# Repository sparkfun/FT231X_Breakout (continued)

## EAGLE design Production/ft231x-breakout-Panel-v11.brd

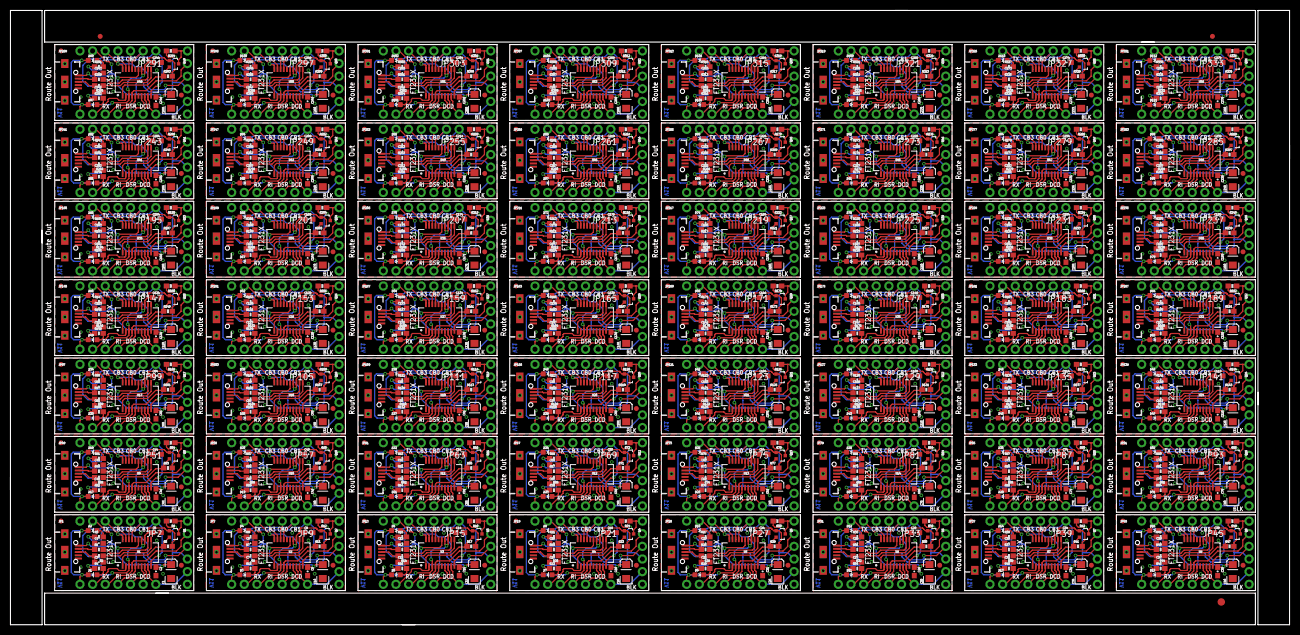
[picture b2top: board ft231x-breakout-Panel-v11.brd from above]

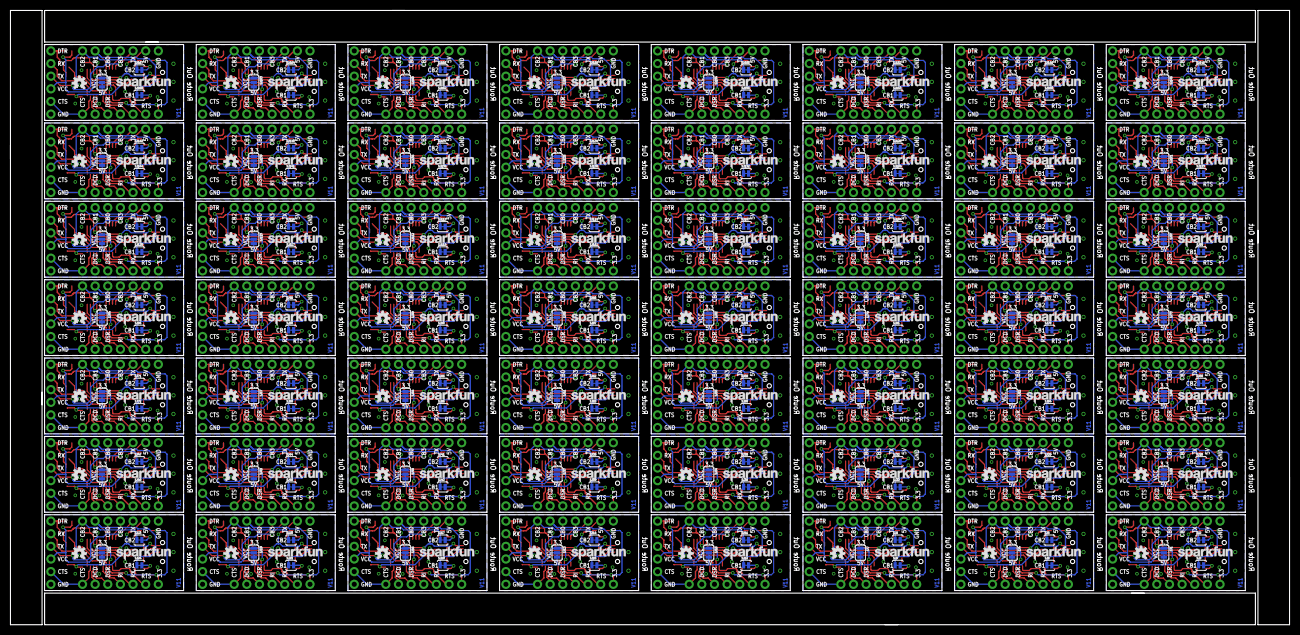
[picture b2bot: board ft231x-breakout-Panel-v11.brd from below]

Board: 2 copper layers, 257.0 x 123.4 mm, 1459 parts (280 on the bottom side), 1400 nets.

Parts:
C1, C10, C15, C20, C25, C30, C35, C40, C45, C50, C55, C60, C65, C70, C75, C80, C85, C90, C95, C100, C105, C110, C115, C120, C125, C130, C135, C140, C145, C150, C155, C160, C165, C170, C175, C180, C185, C190, C195, C200, C205, C210, C215, C220, C225, C230, C235, C240, C245, C250, C255, C260, C265, C270, C275, C280: 10uF; EIA3216
C2, C5, C6, C9, C11, C14, C16, C19, C21, C24, C26, C29, C31, C34, C36, C39, C41, C44, C46, C49, C51, C54, C56, C59, C61, C64, C66, C69, C71, C74, C76, C79, C81, C84, C86, C89, C91, C94, C96, C99, C101, C104, C106, C109, C111, C114, C116, C119, C121, C124, C126, C129, C131, C134, C136, C139, C141, C144, C146, C149, C151, C154, C156, C159, C161, C164, C166, C169, C171, C174, C176, C179, C181, C184, C186, C189, C191, C194, C196, C199, C201, C204, C206, C209, C211, C214, C216, C219, C221, C224, C226, C229, C231, C234, C236, C239, C241, C244, C246, C249, C251, C254, C256, C259, C261, C264, C266, C269, C271, C274, C276, C279: 0.1uF; 0603-CAP
C3, C4, C7, C8, C12, C13, C17, C18, C22, C23, C27, C28, C32, C33, C37, C38, C42, C43, C47, C48, C52, C53, C57, C58, C62, C63, C67, C68, C72, C73, C77, C78, C82, C83, C87, C88, C92, C93, C97, C98, C102, C103, C107, C108, C112, C113, C117, C118, C122, C123, C127, C128, C132, C133, C137, C138, C142, C143, C147, C148, C152, C153, C157, C158, C162, C163, C167, C168, C172, C173, C177, C178, C182, C183, C187, C188, C192, C193, C197, C198, C202, C203, C207, C208, C212, C213, C217, C218, C222, C223, C227, C228, C232, C233, C237, C238, C242, C243, C247, C248, C252, C253, C257, C258, C262, C263, C267, C268, C272, C273, C277, C278: 47pF; 0603-CAP
D1, D3, D5, D7, D9, D11, D13, D15, D17, D19, D21, D23, D25, D27, D29, D31, D33, D35, D37, D39, D41, D43, D45, D47, D49, D51, D53, D55, D57, D59, D61, D63, D65, D67, D69, D71, D73, D75, D77, D79, D81, D83, D85, D87, D89, D91, D93, D95, D97, D99, D101, D103, D105, D107, D109, D111: RED; LED-0603
D2, D4, D6, D8, D10, D12, D14, D16, D18, D20, D22, D24, D26, D28, D30, D32, D34, D36, D38, D40, D42, D44, D46, D48, D50, D52, D54, D56, D58, D60, D62, D64, D66, D68, D70, D72, D74, D76, D78, D80, D82, D84, D86, D88, D90, D92, D94, D96, D98, D100, D102, D104, D106, D108, D110, D112: Yellow; LED-0603
E$1: FIDUCIAL-1.5X3
E$5, E$6: FIDUCIAL-1X2
JP1, JP7, JP13, JP19, JP25, JP31, JP37, JP43, JP49, JP55, JP61, JP67, JP73, JP79, JP85, JP91, JP97, JP103, JP109, JP115, JP121, JP127, JP133, JP139, JP145, JP151, JP157, JP163, JP169, JP175, JP181, JP187, JP193, JP199, JP205, JP211, JP217, JP223, JP229, JP235, JP241, JP247, JP253, JP259, JP265, JP271, JP277, JP283, JP289, JP295, JP301, JP307, JP313, JP319, JP325, JP331: USB-MICROB"; USB-B-MICRO-SMD_V03
JP2, JP4, JP9, JP10, JP15, JP16, JP21, JP22, JP27, JP28, JP33, JP34, JP39, JP40, JP45, JP46, JP51, JP52, JP57, JP58, JP63, JP64, JP69, JP70, JP75, JP76, JP81, JP82, JP87, JP88, JP93, JP94, JP99, JP100, JP105, JP106, JP111, JP112, JP117, JP118, JP123, JP124, JP129, JP130, JP135, JP136, JP141, JP142, JP147, JP148, JP153, JP154, JP159, JP160, JP165, JP166, JP171, JP172, JP177, JP178, JP183, JP184, JP189, JP190, JP195, JP196, JP201, JP202, JP207, JP208, JP213, JP214, JP219, JP220, JP225, JP226, JP231, JP232, JP237, JP238, JP243, JP244, JP249, JP250, JP255, JP256, JP261, JP262, JP267, JP268, JP273, JP274, JP279, JP280, JP285, JP286, JP291, JP292, JP297, JP298, JP303, JP304, JP309, JP310, JP315, JP316, JP321, JP322, JP327, JP328, JP333, JP334: 1X07_NO_SILK
JP3, JP8, JP14, JP20, JP26, JP32, JP38, JP44, JP50, JP56, JP62, JP68, JP74, JP80, JP86, JP92, JP98, JP104, JP110, JP116, JP122, JP128, JP134, JP140, JP146, JP152, JP158, JP164, JP170, JP176, JP182, JP188, JP194, JP200, JP206, JP212, JP218, JP224, JP230, JP236, JP242, JP248, JP254, JP260, JP266, JP272, JP278, JP284, JP290, JP296, JP302, JP308, JP314, JP320, JP326, JP332: 1X06_NO_SILK
JP5, JP6, JP11, JP12, JP17, JP18, JP23, JP24, JP29, JP30, JP35, JP36, JP41, JP42, JP47, JP48, JP53, JP54, JP59, JP60, JP65, JP66, JP71, JP72, JP77, JP78, JP83, JP84, JP89, JP90, JP95, JP96, JP101, JP102, JP107, JP108, JP113, JP114, JP119, JP120, JP125, JP126, JP131, JP132, JP137, JP138, JP143, JP144, JP149, JP150, JP155, JP156, JP161, JP162, JP167, JP168, JP173, JP174, JP179, JP180, JP185, JP186, JP191, JP192, JP197, JP198, JP203, JP204, JP209, JP210, JP215, JP216, JP221, JP222, JP227, JP228, JP233, JP234, JP239, JP240, JP245, JP246, JP251, JP252, JP257, JP258, JP263, JP264, JP269, JP270, JP275, JP276, JP281, JP282, JP287, JP288, JP293, JP294, JP299, JP300, JP305, JP306, JP311, JP312, JP317, JP318, JP323, JP324, JP329, JP330, JP335, JP336: FIDUCIAL1X2; FIDUCIAL-1X2
LOGO1, LOGO2, LOGO3, LOGO4, LOGO5, LOGO6, LOGO7, LOGO8, LOGO9, LOGO10, LOGO11, LOGO12, LOGO13, LOGO14, LOGO15, LOGO16, LOGO17, LOGO18, LOGO19, LOGO20, LOGO21, LOGO22, LOGO23, LOGO24, LOGO25, LOGO26, LOGO27, LOGO28, LOGO29, LOGO30, LOGO31, LOGO32, LOGO33, LOGO34, LOGO35, LOGO36, LOGO37, LOGO38, LOGO39, LOGO40, LOGO41, LOGO42, LOGO43, LOGO44, LOGO45, LOGO46, LOGO47, LOGO48, LOGO49, LOGO50, LOGO51, LOGO52, LOGO53, LOGO54, LOGO55, LOGO56: SFE_LOGO_NAME.1_INCH; SFE_LOGO_NAME_.1
Q1, Q2, Q3, Q4, Q5, Q6, Q7, Q8, Q9, Q10, Q11, Q12, Q13, Q14, Q15, Q16, Q17, Q18, Q19, Q20, Q21, Q22, Q23, Q24, Q25, Q26, Q27, Q28, Q29, Q30, Q31, Q32, Q33, Q34, Q35, Q36, Q37, Q38, Q39, Q40, Q41, Q42, Q43, Q44, Q45, Q46, Q47, Q48, Q49, Q50, Q51, Q52, Q53, Q54, Q55, Q56: 2N7002PW; SOT323
R1, R2, R7, R8, R13, R14, R19, R20, R25, R26, R31, R32, R37, R38, R43, R44, R49, R50, R55, R56, R61, R62, R67, R68, R73, R74, R79, R80, R85, R86, R91, R92, R97, R98, R103, R104, R109, R110, R115, R116, R121, R122, R127, R128, R133, R134, R139, R140, R145, R146, R151, R152, R157, R158, R163, R164, R169, R170, R175, R176, R181, R182, R187, R188, R193, R194, R199, R200, R205, R206, R211, R212, R217, R218, R223, R224, R229, R230, R235, R236, R241, R242, R247, R248, R253, R254, R259, R260, R265, R266, R271, R272, R277, R278, R283, R284, R289, R290, R295, R296, R301, R302, R307, R308, R313, R314, R319, R320, R325, R326, R331, R332: 27; 0603-RES
R3, R4, R9, R10, R15, R16, R21, R22, R27, R28, R33, R34, R39, R40, R45, R46, R51, R52, R57, R58, R63, R64, R69, R70, R75, R76, R81, R82, R87, R88, R93, R94, R99, R100, R105, R106, R111, R112, R117, R118, R123, R124, R129, R130, R135, R136, R141, R142, R147, R148, R153, R154, R159, R160, R165, R166, R171, R172, R177, R178, R183, R184, R189, R190, R195, R196, R201, R202, R207, R208, R213, R214, R219, R220, R225, R226, R231, R232, R237, R238, R243, R244, R249, R250, R255, R256, R261, R262, R267, R268, R273, R274, R279, R280, R285, R286, R291, R292, R297, R298, R303, R304, R309, R310, R315, R316, R321, R322, R327, R328, R333, R334: 1K; 0603-RES
R5, R6, R11, R12, R17, R18, R23, R24, R29, R30, R35, R36, R41, R42, R47, R48, R53, R54, R59, R60, R65, R66, R71, R72, R77, R78, R83, R84, R89, R90, R95, R96, R101, R102, R107, R108, R113, R114, R119, R120, R125, R126, R131, R132, R137, R138, R143, R144, R149, R150, R155, R156, R161, R162, R167, R168, R173, R174, R179, R180, R185, R186, R191, R192, R197, R198, R203, R204, R209, R210, R215, R216, R221, R222, R227, R228, R233, R234, R239, R240, R245, R246, R251, R252, R257, R258, R263, R264, R269, R270, R275, R276, R281, R282, R287, R288, R293, R294, R299, R300, R305, R306, R311, R312, R317, R318, R323, R324, R329, R330, R335, R336: 10k; 0603-RES@1
SJ1, SJ4, SJ7, SJ10, SJ13, SJ16, SJ19, SJ22, SJ25, SJ28, SJ31, SJ34, SJ37, SJ40, SJ43, SJ46, SJ49, SJ52, SJ55, SJ58, SJ61, SJ64, SJ67, SJ70, SJ73, SJ76, SJ79, SJ82, SJ85, SJ88, SJ91, SJ94, SJ97, SJ100, SJ103, SJ106, SJ109, SJ112, SJ115, SJ118, SJ121, SJ124, SJ127, SJ130, SJ133, SJ136, SJ139, SJ142, SJ145, SJ148, SJ151, SJ154, SJ157, SJ160, SJ163, SJ166: SJ_3
SJ2, SJ5, SJ8, SJ11, SJ14, SJ17, SJ20, SJ23, SJ26, SJ29, SJ32, SJ35, SJ38, SJ41, SJ44, SJ47, SJ50, SJ53, SJ56, SJ59, SJ62, SJ65, SJ68, SJ71, SJ74, SJ77, SJ80, SJ83, SJ86, SJ89, SJ92, SJ95, SJ98, SJ101, SJ104, SJ107, SJ110, SJ113, SJ116, SJ119, SJ122, SJ125, SJ128, SJ131, SJ134, SJ137, SJ140, SJ143, SJ146, SJ149, SJ152, SJ155, SJ158, SJ161, SJ164, SJ167: TXLED; SJ_2S-TRACE
SJ3, SJ6, SJ9, SJ12, SJ15, SJ18, SJ21, SJ24, SJ27, SJ30, SJ33, SJ36, SJ39, SJ42, SJ45, SJ48, SJ51, SJ54, SJ57, SJ60, SJ63, SJ66, SJ69, SJ72, SJ75, SJ78, SJ81, SJ84, SJ87, SJ90, SJ93, SJ96, SJ99, SJ102, SJ105, SJ108, SJ111, SJ114, SJ117, SJ120, SJ123, SJ126, SJ129, SJ132, SJ135, SJ138, SJ141, SJ144, SJ147, SJ150, SJ153, SJ156, SJ159, SJ162, SJ165, SJ168: RXLED; PAD-JUMPER-2-NC_BY_TRACE_YES_SILK
U1, U2, U3, U4, U5, U6, U7, U8, U9, U10, U11, U12, U13, U14, U15, U16, U17, U18, U19, U20, U21, U22, U23, U24, U25, U26, U27, U28, U29, U30, U31, U32, U33, U34, U35, U36, U37, U38, U39, U40, U41, U42, U43, U44, U45, U46, U47, U48, U49, U50, U51, U52, U53, U54, U55, U56: FTS31XS-U; SSOP20_L
U$1, U$2, U$3, U$4, U$5, U$6, U$7, U$8, U$9, U$10, U$11, U$12, U$13, U$14, U$15, U$16, U$17, U$18, U$19, U$20, U$21, U$22, U$23, U$24, U$25, U$26, U$27, U$28, U$29, U$30, U$31, U$32, U$33, U$34, U$35, U$36, U$37, U$38, U$39, U$40, U$41, U$42, U$43, U$44, U$45, U$46, U$47, U$48, U$49, U$50, U$51, U$52, U$53, U$54, U$55, U$56: OSHW-LOGOS; OSHW-LOGO-S

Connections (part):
3.3V: C5.1, D1.A, D2.A, JP4.7, Q1.1, R5.2, SJ1.1, U1.3, U1.13, U1.14
3.3V1: C9.1, D3.A, D4.A, JP10.7, Q2.1, R11.2, SJ4.1, U2.3, U2.13, U2.14
3.3V2: C14.1, D5.A, D6.A, JP16.7, Q3.1, R17.2, SJ7.1, U3.3, U3.13, U3.14
3.3V3: C19.1, D7.A, D8.A, JP22.7, Q4.1, R23.2, SJ10.1, U4.3, U4.13, U4.14
3.3V4: C24.1, D9.A, D10.A, JP28.7, Q5.1, R29.2, SJ13.1, U5.3, U5.13, U5.14
3.3V5: C29.1, D11.A, D12.A, JP34.7, Q6.1, R35.2, SJ16.1, U6.3, U6.13, U6.14
3.3V6: C34.1, D13.A, D14.A, JP40.7, Q7.1, R41.2, SJ19.1, U7.3, U7.13, U7.14
3.3V7: C39.1, D15.A, D16.A, JP46.7, Q8.1, R47.2, SJ22.1, U8.3, U8.13, U8.14
3.3V8: C44.1, D17.A, D18.A, JP52.7, Q9.1, R53.2, SJ25.1, U9.3, U9.13, U9.14
3.3V9: C49.1, D19.A, D20.A, JP58.7, Q10.1, R59.2, SJ28.1, U10.3, U10.13, U10.14
3.3V10: C54.1, D21.A, D22.A, JP64.7, Q11.1, R65.2, SJ31.1, U11.3, U11.13, U11.14
3.3V11: C59.1, D23.A, D24.A, JP70.7, Q12.1, R71.2, SJ34.1, U12.3, U12.13, U12.14
3.3V12: C64.1, D25.A, D26.A, JP76.7, Q13.1, R77.2, SJ37.1, U13.3, U13.13, U13.14
3.3V13: C69.1, D27.A, D28.A, JP82.7, Q14.1, R83.2, SJ40.1, U14.3, U14.13, U14.14
3.3V14: C74.1, D29.A, D30.A, JP88.7, Q15.1, R89.2, SJ43.1, U15.3, U15.13, U15.14
3.3V15: C79.1, D31.A, D32.A, JP94.7, Q16.1, R95.2, SJ46.1, U16.3, U16.13, U16.14
3.3V16: C84.1, D33.A, D34.A, JP100.7, Q17.1, R101.2, SJ49.1, U17.3, U17.13, U17.14
3.3V17: C89.1, D35.A, D36.A, JP106.7, Q18.1, R107.2, SJ52.1, U18.3, U18.13, U18.14
3.3V18: C94.1, D37.A, D38.A, JP112.7, Q19.1, R113.2, SJ55.1, U19.3, U19.13, U19.14
3.3V19: C99.1, D39.A, D40.A, JP118.7, Q20.1, R119.2, SJ58.1, U20.3, U20.13, U20.14
3.3V20: C104.1, D41.A, D42.A, JP124.7, Q21.1, R125.2, SJ61.1, U21.3, U21.13, U21.14
3.3V21: C109.1, D43.A, D44.A, JP130.7, Q22.1, R131.2, SJ64.1, U22.3, U22.13, U22.14
3.3V22: C114.1, D45.A, D46.A, JP136.7, Q23.1, R137.2, SJ67.1, U23.3, U23.13, U23.14
3.3V23: C119.1, D47.A, D48.A, JP142.7, Q24.1, R143.2, SJ70.1, U24.3, U24.13, U24.14
3.3V24: C124.1, D49.A, D50.A, JP148.7, Q25.1, R149.2, SJ73.1, U25.3, U25.13, U25.14
3.3V25: C129.1, D51.A, D52.A, JP154.7, Q26.1, R155.2, SJ76.1, U26.3, U26.13, U26.14
3.3V26: C134.1, D53.A, D54.A, JP160.7, Q27.1, R161.2, SJ79.1, U27.3, U27.13, U27.14
3.3V27: C139.1, D55.A, D56.A, JP166.7, Q28.1, R167.2, SJ82.1, U28.3, U28.13, U28.14
3.3V28: C144.1, D57.A, D58.A, JP172.7, Q29.1, R173.2, SJ85.1, U29.3, U29.13, U29.14
3.3V29: C149.1, D59.A, D60.A, JP178.7, Q30.1, R179.2, SJ88.1, U30.3, U30.13, U30.14
3.3V30: C154.1, D61.A, D62.A, JP184.7, Q31.1, R185.2, SJ91.1, U31.3, U31.13, U31.14
3.3V31: C159.1, D63.A, D64.A, JP190.7, Q32.1, R191.2, SJ94.1, U32.3, U32.13, U32.14
3.3V32: C164.1, D65.A, D66.A, JP196.7, Q33.1, R197.2, SJ97.1, U33.3, U33.13, U33.14
3.3V33: C169.1, D67.A, D68.A, JP202.7, Q34.1, R203.2, SJ100.1, U34.3, U34.13, U34.14
3.3V34: C174.1, D69.A, D70.A, JP208.7, Q35.1, R209.2, SJ103.1, U35.3, U35.13, U35.14
3.3V35: C179.1, D71.A, D72.A, JP214.7, Q36.1, R215.2, SJ106.1, U36.3, U36.13, U36.14
3.3V36: C184.1, D73.A, D74.A, JP220.7, Q37.1, R221.2, SJ109.1, U37.3, U37.13, U37.14
3.3V37: C189.1, D75.A, D76.A, JP226.7, Q38.1, R227.2, SJ112.1, U38.3, U38.13, U38.14
3.3V38: C194.1, D77.A, D78.A, JP232.7, Q39.1, R233.2, SJ115.1, U39.3, U39.13, U39.14
3.3V39: C199.1, D79.A, D80.A, JP238.7, Q40.1, R239.2, SJ118.1, U40.3, U40.13, U40.14
3.3V40: C204.1, D81.A, D82.A, JP244.7, Q41.1, R245.2, SJ121.1, U41.3, U41.13, U41.14
3.3V41: C209.1, D83.A, D84.A, JP250.7, Q42.1, R251.2, SJ124.1, U42.3, U42.13, U42.14
3.3V42: C214.1, D85.A, D86.A, JP256.7, Q43.1, R257.2, SJ127.1, U43.3, U43.13, U43.14
3.3V43: C219.1, D87.A, D88.A, JP262.7, Q44.1, R263.2, SJ130.1, U44.3, U44.13, U44.14
3.3V44: C224.1, D89.A, D90.A, JP268.7, Q45.1, R269.2, SJ133.1, U45.3, U45.13, U45.14
3.3V45: C229.1, D91.A, D92.A, JP274.7, Q46.1, R275.2, SJ136.1, U46.3, U46.13, U46.14
3.3V46: C234.1, D93.A, D94.A, JP280.7, Q47.1, R281.2, SJ139.1, U47.3, U47.13, U47.14
3.3V47: C239.1, D95.A, D96.A, JP286.7, Q48.1, R287.2, SJ142.1, U48.3, U48.13, U48.14
3.3V48: C244.1, D97.A, D98.A, JP292.7, Q49.1, R293.2, SJ145.1, U49.3, U49.13, U49.14
3.3V49: C249.1, D99.A, D100.A, JP298.7, Q50.1, R299.2, SJ148.1, U50.3, U50.13, U50.14
3.3V50: C254.1, D101.A, D102.A, JP304.7, Q51.1, R305.2, SJ151.1, U51.3, U51.13, U51.14
3.3V51: C259.1, D103.A, D104.A, JP310.7, Q52.1, R311.2, SJ154.1, U52.3, U52.13, U52.14
3.3V52: C264.1, D105.A, D106.A, JP316.7, Q53.1, R317.2, SJ157.1, U53.3, U53.13, U53.14
3.3V53: C269.1, D107.A, D108.A, JP322.7, Q54.1, R323.2, SJ160.1, U54.3, U54.13, U54.14
3.3V54: C274.1, D109.A, D110.A, JP328.7, Q55.1, R329.2, SJ163.1, U55.3, U55.13, U55.14
3.3V55: C279.1, D111.A, D112.A, JP334.7, Q56.1, R335.2, SJ166.1, U56.3, U56.13, U56.14
CBUS0: JP2.3, U1.18
CBUS1: JP9.4, U2.19
CBUS2: JP9.3, U2.18
CBUS3: JP2.4, U1.19
CBUS4: JP15.4, U3.19
CBUS5: JP15.3, U3.18
CBUS6: JP21.4, U4.19
CBUS7: JP21.3, U4.18
CBUS8: JP27.4, U5.19
CBUS9: JP27.3, U5.18
CBUS10: JP33.4, U6.19
CBUS11: JP33.3, U6.18
CBUS12: JP39.4, U7.19
CBUS13: JP39.3, U7.18
CBUS14: JP45.4, U8.19
CBUS15: JP45.3, U8.18
CBUS16: JP51.4, U9.19
CBUS17: JP51.3, U9.18
CBUS18: JP57.4, U10.19
CBUS19: JP57.3, U10.18
CBUS20: JP63.4, U11.19
CBUS21: JP63.3, U11.18
CBUS22: JP69.4, U12.19
CBUS23: JP69.3, U12.18
CBUS24: JP75.4, U13.19
CBUS25: JP75.3, U13.18
CBUS26: JP81.4, U14.19
CBUS27: JP81.3, U14.18
CBUS28: JP87.4, U15.19
CBUS29: JP87.3, U15.18
CBUS30: JP93.4, U16.19
CBUS31: JP93.3, U16.18
CBUS32: JP99.4, U17.19
CBUS33: JP99.3, U17.18
CBUS34: JP105.4, U18.19
CBUS35: JP105.3, U18.18
CBUS36: JP111.4, U19.19
CBUS37: JP111.3, U19.18
CBUS38: JP117.4, U20.19
CBUS39: JP117.3, U20.18
CBUS40: JP123.4, U21.19
CBUS41: JP123.3, U21.18
CBUS42: JP129.4, U22.19
CBUS43: JP129.3, U22.18
CBUS44: JP135.4, U23.19
CBUS45: JP135.3, U23.18
CBUS46: JP141.4, U24.19
CBUS47: JP141.3, U24.18
CBUS48: JP147.4, U25.19
CBUS49: JP147.3, U25.18
CBUS50: JP153.4, U26.19
CBUS51: JP153.3, U26.18
CBUS52: JP159.4, U27.19
CBUS53: JP159.3, U27.18
CBUS54: JP165.4, U28.19
CBUS55: JP165.3, U28.18
CBUS56: JP171.4, U29.19
CBUS57: JP171.3, U29.18
CBUS58: JP177.4, U30.19
CBUS59: JP177.3, U30.18
CBUS60: JP183.4, U31.19
CBUS61: JP183.3, U31.18
CBUS62: JP189.4, U32.19
CBUS63: JP189.3, U32.18
CBUS64: JP195.4, U33.19
CBUS65: JP195.3, U33.18
CBUS66: JP201.4, U34.19
CBUS67: JP201.3, U34.18
CBUS68: JP207.4, U35.19
CBUS69: JP207.3, U35.18
CBUS70: JP213.4, U36.19
CBUS71: JP213.3, U36.18
CBUS72: JP219.4, U37.19
CBUS73: JP219.3, U37.18
CBUS74: JP225.4, U38.19
CBUS75: JP225.3, U38.18
CBUS76: JP231.4, U39.19
CBUS77: JP231.3, U39.18
CBUS78: JP237.4, U40.19
CBUS79: JP237.3, U40.18
CBUS80: JP243.4, U41.19
CBUS81: JP243.3, U41.18
CBUS82: JP249.4, U42.19
CBUS83: JP249.3, U42.18
CBUS84: JP255.4, U43.19
CBUS85: JP255.3, U43.18
CBUS86: JP261.4, U44.19
CBUS87: JP261.3, U44.18
CBUS88: JP267.4, U45.19
CBUS89: JP267.3, U45.18
CBUS90: JP273.4, U46.19
CBUS91: JP273.3, U46.18
CBUS92: JP279.4, U47.19
CBUS93: JP279.3, U47.18
CBUS94: JP285.4, U48.19
CBUS95: JP285.3, U48.18
CBUS96: JP291.4, U49.19
CBUS97: JP291.3, U49.18
CBUS98: JP297.4, U50.19
CBUS99: JP297.3, U50.18
CBUS100: JP303.4, U51.19
CBUS101: JP303.3, U51.18
CBUS102: JP309.4, U52.19
CBUS103: JP309.3, U52.18
CBUS104: JP315.4, U53.19
CBUS105: JP315.3, U53.18
CBUS106: JP321.4, U54.19
CBUS107: JP321.3, U54.18
CBUS108: JP327.4, U55.19
CBUS109: JP327.3, U55.18
CBUS110: JP333.4, U56.19
CBUS111: JP333.3, U56.18
CTS: JP3.2, JP4.1, U1.9
CTS1: JP8.2, JP10.1, U2.9
CTS2: JP14.2, JP16.1, U3.9
CTS3: JP20.2, JP22.1, U4.9
CTS4: JP26.2, JP28.1, U5.9
CTS5: JP32.2, JP34.1, U6.9
CTS6: JP38.2, JP40.1, U7.9
CTS7: JP44.2, JP46.1, U8.9
CTS8: JP50.2, JP52.1, U9.9
CTS9: JP56.2, JP58.1, U10.9
CTS10: JP62.2, JP64.1, U11.9
CTS11: JP68.2, JP70.1, U12.9
CTS12: JP74.2, JP76.1, U13.9
CTS13: JP80.2, JP82.1, U14.9
CTS14: JP86.2, JP88.1, U15.9
CTS15: JP92.2, JP94.1, U16.9
CTS16: JP98.2, JP100.1, U17.9
CTS17: JP104.2, JP106.1, U18.9
CTS18: JP110.2, JP112.1, U19.9
CTS19: JP116.2, JP118.1, U20.9
CTS20: JP122.2, JP124.1, U21.9
CTS21: JP128.2, JP130.1, U22.9
CTS22: JP134.2, JP136.1, U23.9
CTS23: JP140.2, JP142.1, U24.9
CTS24: JP146.2, JP148.1, U25.9
CTS25: JP152.2, JP154.1, U26.9
CTS26: JP158.2, JP160.1, U27.9
CTS27: JP164.2, JP166.1, U28.9
CTS28: JP170.2, JP172.1, U29.9
CTS29: JP176.2, JP178.1, U30.9
CTS30: JP182.2, JP184.1, U31.9
CTS31: JP188.2, JP190.1, U32.9
CTS32: JP194.2, JP196.1, U33.9
CTS33: JP200.2, JP202.1, U34.9
CTS34: JP206.2, JP208.1, U35.9
CTS35: JP212.2, JP214.1, U36.9
CTS36: JP218.2, JP220.1, U37.9
CTS37: JP224.2, JP226.1, U38.9
CTS38: JP230.2, JP232.1, U39.9
CTS39: JP236.2, JP238.1, U40.9
CTS40: JP242.2, JP244.1, U41.9
CTS41: JP248.2, JP250.1, U42.9
CTS42: JP254.2, JP256.1, U43.9
CTS43: JP260.2, JP262.1, U44.9
CTS44: JP266.2, JP268.1, U45.9
CTS45: JP272.2, JP274.1, U46.9
CTS46: JP278.2, JP280.1, U47.9
CTS47: JP284.2, JP286.1, U48.9
CTS48: JP290.2, JP292.1, U49.9
CTS49: JP296.2, JP298.1, U50.9
CTS50: JP302.2, JP304.1, U51.9
CTS51: JP308.2, JP310.1, U52.9
CTS52: JP314.2, JP316.1, U53.9
CTS53: JP320.2, JP322.1, U54.9
CTS54: JP326.2, JP328.1, U55.9
CTS55: JP332.2, JP334.1, U56.9
DCD: JP4.2, U1.8
DCD1: JP10.2, U2.8
DCD2: JP16.2, U3.8
DCD3: JP22.2, U4.8
DCD4: JP28.2, U5.8
DCD5: JP34.2, U6.8
DCD6: JP40.2, U7.8
DCD7: JP46.2, U8.8
DCD8: JP52.2, U9.8
DCD9: JP58.2, U10.8
DCD10: JP64.2, U11.8
DCD11: JP70.2, U12.8
DCD12: JP76.2, U13.8
DCD13: JP82.2, U14.8
DCD14: JP88.2, U15.8
DCD15: JP94.2, U16.8
DCD16: JP100.2, U17.8
DCD17: JP106.2, U18.8
DCD18: JP112.2, U19.8
DCD19: JP118.2, U20.8
DCD20: JP124.2, U21.8
DCD21: JP130.2, U22.8
DCD22: JP136.2, U23.8
DCD23: JP142.2, U24.8
DCD24: JP148.2, U25.8
DCD25: JP154.2, U26.8
DCD26: JP160.2, U27.8
DCD27: JP166.2, U28.8
DCD28: JP172.2, U29.8
DCD29: JP178.2, U30.8
DCD30: JP184.2, U31.8
DCD31: JP190.2, U32.8
DCD32: JP196.2, U33.8
DCD33: JP202.2, U34.8
DCD34: JP208.2, U35.8
DCD35: JP214.2, U36.8
DCD36: JP220.2, U37.8
DCD37: JP226.2, U38.8
DCD38: JP232.2, U39.8
DCD39: JP238.2, U40.8
DCD40: JP244.2, U41.8
DCD41: JP250.2, U42.8
DCD42: JP256.2, U43.8
DCD43: JP262.2, U44.8
DCD44: JP268.2, U45.8
DCD45: JP274.2, U46.8
DCD46: JP280.2, U47.8
DCD47: JP286.2, U48.8
DCD48: JP292.2, U49.8
DCD49: JP298.2, U50.8
DCD50: JP304.2, U51.8
DCD51: JP310.2, U52.8
DCD52: JP316.2, U53.8
DCD53: JP322.2, U54.8
DCD54: JP328.2, U55.8
DCD55: JP334.2, U56.8
DSR: JP4.3, U1.7
DSR1: JP10.3, U2.7
DSR2: JP16.3, U3.7
DSR3: JP22.3, U4.7
DSR4: JP28.3, U5.7
DSR5: JP34.3, U6.7
DSR6: JP40.3, U7.7
DSR7: JP46.3, U8.7
DSR8: JP52.3, U9.7
DSR9: JP58.3, U10.7
DSR10: JP64.3, U11.7
DSR11: JP70.3, U12.7
DSR12: JP76.3, U13.7
DSR13: JP82.3, U14.7
DSR14: JP88.3, U15.7
DSR15: JP94.3, U16.7
DSR16: JP100.3, U17.7
DSR17: JP106.3, U18.7
DSR18: JP112.3, U19.7
DSR19: JP118.3, U20.7
DSR20: JP124.3, U21.7
DSR21: JP130.3, U22.7
DSR22: JP136.3, U23.7
DSR23: JP142.3, U24.7
DSR24: JP148.3, U25.7
DSR25: JP154.3, U26.7
DSR26: JP160.3, U27.7
DSR27: JP166.3, U28.7
DSR28: JP172.3, U29.7
DSR29: JP178.3, U30.7
DSR30: JP184.3, U31.7
DSR31: JP190.3, U32.7
DSR32: JP196.3, U33.7
DSR33: JP202.3, U34.7
DSR34: JP208.3, U35.7
DSR35: JP214.3, U36.7
DSR36: JP220.3, U37.7
DSR37: JP226.3, U38.7
DSR38: JP232.3, U39.7
DSR39: JP238.3, U40.7
DSR40: JP244.3, U41.7
DSR41: JP250.3, U42.7
DSR42: JP256.3, U43.7
DSR43: JP262.3, U44.7
DSR44: JP268.3, U45.7
DSR45: JP274.3, U46.7
DSR46: JP280.3, U47.7
DSR47: JP286.3, U48.7
DSR48: JP292.3, U49.7
DSR49: JP298.3, U50.7
DSR50: JP304.3, U51.7
DSR51: JP310.3, U52.7
DSR52: JP316.3, U53.7
DSR53: JP322.3, U54.7
DSR54: JP328.3, U55.7
DSR55: JP334.3, U56.7
DTR: Q1.2, R5.1, U1.1
DTR1: Q2.2, R11.1, U2.1
DTR2: Q3.2, R17.1, U3.1
DTR3: Q4.2, R23.1, U4.1
DTR4: Q5.2, R29.1, U5.1
DTR5: Q6.2, R35.1, U6.1
DTR6: Q7.2, R41.1, U7.1
DTR7: Q8.2, R47.1, U8.1
DTR8: Q9.2, R53.1, U9.1
DTR9: Q10.2, R59.1, U10.1
DTR10: Q11.2, R65.1, U11.1
DTR11: Q12.2, R71.1, U12.1
DTR12: Q13.2, R77.1, U13.1
DTR13: Q14.2, R83.1, U14.1
DTR14: Q15.2, R89.1, U15.1
DTR15: Q16.2, R95.1, U16.1
DTR16: Q17.2, R101.1, U17.1
DTR17: Q18.2, R107.1, U18.1
DTR18: Q19.2, R113.1, U19.1
DTR19: Q20.2, R119.1, U20.1
DTR20: Q21.2, R125.1, U21.1
DTR21: Q22.2, R131.1, U22.1
DTR22: Q23.2, R137.1, U23.1
DTR23: Q24.2, R143.1, U24.1
DTR24: Q25.2, R149.1, U25.1
DTR25: Q26.2, R155.1, U26.1
DTR26: Q27.2, R161.1, U27.1
DTR27: Q28.2, R167.1, U28.1
DTR28: Q29.2, R173.1, U29.1
DTR29: Q30.2, R179.1, U30.1
DTR30: Q31.2, R185.1, U31.1
DTR31: Q32.2, R191.1, U32.1
DTR32: Q33.2, R197.1, U33.1
DTR33: Q34.2, R203.1, U34.1
DTR34: Q35.2, R209.1, U35.1
DTR35: Q36.2, R215.1, U36.1
DTR36: Q37.2, R221.1, U37.1
DTR37: Q38.2, R227.1, U38.1
DTR38: Q39.2, R233.1, U39.1
DTR39: Q40.2, R239.1, U40.1
DTR40: Q41.2, R245.1, U41.1
DTR41: Q42.2, R251.1, U42.1
DTR42: Q43.2, R257.1, U43.1
DTR43: Q44.2, R263.1, U44.1
DTR44: Q45.2, R269.1, U45.1
DTR45: Q46.2, R275.1, U46.1
DTR46: Q47.2, R281.1, U47.1
DTR47: Q48.2, R287.1, U48.1
DTR48: Q49.2, R293.1, U49.1
DTR49: Q50.2, R299.1, U50.1
DTR50: Q51.2, R305.1, U51.1
DTR51: Q52.2, R311.1, U52.1
DTR52: Q53.2, R317.1, U53.1
DTR53: Q54.2, R323.1, U54.1
DTR54: Q55.2, R329.1, U55.1
DTR55: Q56.2, R335.1, U56.1
GND: C1.C, C2.2, C3.2, C4.2, C5.2, JP1.GND1, JP1.SHIELD1, JP1.SHIELD2, JP1.SHIELD3, JP2.7, JP3.1, U1.6, U1.16
GND1: C6.2, C7.2, C8.2, C9.2, C10.C, JP7.GND1, JP7.SHIELD1, JP7.SHIELD2, JP7.SHIELD3, JP8.1, JP9.7, U2.6, U2.16
GND2: C11.2, C12.2, C13.2, C14.2, C15.C, JP13.GND1, JP13.SHIELD1, JP13.SHIELD2, JP13.SHIELD3, JP14.1, JP15.7, U3.6, U3.16
GND3: C16.2, C17.2, C18.2, C19.2, C20.C, JP19.GND1, JP19.SHIELD1, JP19.SHIELD2, JP19.SHIELD3, JP20.1, JP21.7, U4.6, U4.16
GND4: C21.2, C22.2, C23.2, C24.2, C25.C, JP25.GND1, JP25.SHIELD1, JP25.SHIELD2, JP25.SHIELD3, JP26.1, JP27.7, U5.6, U5.16
GND5: C26.2, C27.2, C28.2, C29.2, C30.C, JP31.GND1, JP31.SHIELD1, JP31.SHIELD2, JP31.SHIELD3, JP32.1, JP33.7, U6.6, U6.16
GND6: C31.2, C32.2, C33.2, C34.2, C35.C, JP37.GND1, JP37.SHIELD1, JP37.SHIELD2, JP37.SHIELD3, JP38.1, JP39.7, U7.6, U7.16
GND7: C36.2, C37.2, C38.2, C39.2, C40.C, JP43.GND1, JP43.SHIELD1, JP43.SHIELD2, JP43.SHIELD3, JP44.1, JP45.7, U8.6, U8.16
GND8: C41.2, C42.2, C43.2, C44.2, C45.C, JP49.GND1, JP49.SHIELD1, JP49.SHIELD2, JP49.SHIELD3, JP50.1, JP51.7, U9.6, U9.16
GND9: C46.2, C47.2, C48.2, C49.2, C50.C, JP55.GND1, JP55.SHIELD1, JP55.SHIELD2, JP55.SHIELD3, JP56.1, JP57.7, U10.6, U10.16
GND10: C51.2, C52.2, C53.2, C54.2, C55.C, JP61.GND1, JP61.SHIELD1, JP61.SHIELD2, JP61.SHIELD3, JP62.1, JP63.7, U11.6, U11.16
GND11: C56.2, C57.2, C58.2, C59.2, C60.C, JP67.GND1, JP67.SHIELD1, JP67.SHIELD2, JP67.SHIELD3, JP68.1, JP69.7, U12.6, U12.16
GND12: C61.2, C62.2, C63.2, C64.2, C65.C, JP73.GND1, JP73.SHIELD1, JP73.SHIELD2, JP73.SHIELD3, JP74.1, JP75.7, U13.6, U13.16
GND13: C66.2, C67.2, C68.2, C69.2, C70.C, JP79.GND1, JP79.SHIELD1, JP79.SHIELD2, JP79.SHIELD3, JP80.1, JP81.7, U14.6, U14.16
GND14: C71.2, C72.2, C73.2, C74.2, C75.C, JP85.GND1, JP85.SHIELD1, JP85.SHIELD2, JP85.SHIELD3, JP86.1, JP87.7, U15.6, U15.16
GND15: C76.2, C77.2, C78.2, C79.2, C80.C, JP91.GND1, JP91.SHIELD1, JP91.SHIELD2, JP91.SHIELD3, JP92.1, JP93.7, U16.6, U16.16
GND16: C81.2, C82.2, C83.2, C84.2, C85.C, JP97.GND1, JP97.SHIELD1, JP97.SHIELD2, JP97.SHIELD3, JP98.1, JP99.7, U17.6, U17.16
GND17: C86.2, C87.2, C88.2, C89.2, C90.C, JP103.GND1, JP103.SHIELD1, JP103.SHIELD2, JP103.SHIELD3, JP104.1, JP105.7, U18.6, U18.16
GND18: C91.2, C92.2, C93.2, C94.2, C95.C, JP109.GND1, JP109.SHIELD1, JP109.SHIELD2, JP109.SHIELD3, JP110.1, JP111.7, U19.6, U19.16
GND19: C96.2, C97.2, C98.2, C99.2, C100.C, JP115.GND1, JP115.SHIELD1, JP115.SHIELD2, JP115.SHIELD3, JP116.1, JP117.7, U20.6, U20.16
GND20: C101.2, C102.2, C103.2, C104.2, C105.C, JP121.GND1, JP121.SHIELD1, JP121.SHIELD2, JP121.SHIELD3, JP122.1, JP123.7, U21.6, U21.16
GND21: C106.2, C107.2, C108.2, C109.2, C110.C, JP127.GND1, JP127.SHIELD1, JP127.SHIELD2, JP127.SHIELD3, JP128.1, JP129.7, U22.6, U22.16
GND22: C111.2, C112.2, C113.2, C114.2, C115.C, JP133.GND1, JP133.SHIELD1, JP133.SHIELD2, JP133.SHIELD3, JP134.1, JP135.7, U23.6, U23.16
GND23: C116.2, C117.2, C118.2, C119.2, C120.C, JP139.GND1, JP139.SHIELD1, JP139.SHIELD2, JP139.SHIELD3, JP140.1, JP141.7, U24.6, U24.16
GND24: C121.2, C122.2, C123.2, C124.2, C125.C, JP145.GND1, JP145.SHIELD1, JP145.SHIELD2, JP145.SHIELD3, JP146.1, JP147.7, U25.6, U25.16
GND25: C126.2, C127.2, C128.2, C129.2, C130.C, JP151.GND1, JP151.SHIELD1, JP151.SHIELD2, JP151.SHIELD3, JP152.1, JP153.7, U26.6, U26.16
GND26: C131.2, C132.2, C133.2, C134.2, C135.C, JP157.GND1, JP157.SHIELD1, JP157.SHIELD2, JP157.SHIELD3, JP158.1, JP159.7, U27.6, U27.16
GND27: C136.2, C137.2, C138.2, C139.2, C140.C, JP163.GND1, JP163.SHIELD1, JP163.SHIELD2, JP163.SHIELD3, JP164.1, JP165.7, U28.6, U28.16
GND28: C141.2, C142.2, C143.2, C144.2, C145.C, JP169.GND1, JP169.SHIELD1, JP169.SHIELD2, JP169.SHIELD3, JP170.1, JP171.7, U29.6, U29.16
GND29: C146.2, C147.2, C148.2, C149.2, C150.C, JP175.GND1, JP175.SHIELD1, JP175.SHIELD2, JP175.SHIELD3, JP176.1, JP177.7, U30.6, U30.16
GND30: C151.2, C152.2, C153.2, C154.2, C155.C, JP181.GND1, JP181.SHIELD1, JP181.SHIELD2, JP181.SHIELD3, JP182.1, JP183.7, U31.6, U31.16
GND31: C156.2, C157.2, C158.2, C159.2, C160.C, JP187.GND1, JP187.SHIELD1, JP187.SHIELD2, JP187.SHIELD3, JP188.1, JP189.7, U32.6, U32.16
GND32: C161.2, C162.2, C163.2, C164.2, C165.C, JP193.GND1, JP193.SHIELD1, JP193.SHIELD2, JP193.SHIELD3, JP194.1, JP195.7, U33.6, U33.16
GND33: C166.2, C167.2, C168.2, C169.2, C170.C, JP199.GND1, JP199.SHIELD1, JP199.SHIELD2, JP199.SHIELD3, JP200.1, JP201.7, U34.6, U34.16
GND34: C171.2, C172.2, C173.2, C174.2, C175.C, JP205.GND1, JP205.SHIELD1, JP205.SHIELD2, JP205.SHIELD3, JP206.1, JP207.7, U35.6, U35.16
GND35: C176.2, C177.2, C178.2, C179.2, C180.C, JP211.GND1, JP211.SHIELD1, JP211.SHIELD2, JP211.SHIELD3, JP212.1, JP213.7, U36.6, U36.16
GND36: C181.2, C182.2, C183.2, C184.2, C185.C, JP217.GND1, JP217.SHIELD1, JP217.SHIELD2, JP217.SHIELD3, JP218.1, JP219.7, U37.6, U37.16
GND37: C186.2, C187.2, C188.2, C189.2, C190.C, JP223.GND1, JP223.SHIELD1, JP223.SHIELD2, JP223.SHIELD3, JP224.1, JP225.7, U38.6, U38.16
GND38: C191.2, C192.2, C193.2, C194.2, C195.C, JP229.GND1, JP229.SHIELD1, JP229.SHIELD2, JP229.SHIELD3, JP230.1, JP231.7, U39.6, U39.16
GND39: C196.2, C197.2, C198.2, C199.2, C200.C, JP235.GND1, JP235.SHIELD1, JP235.SHIELD2, JP235.SHIELD3, JP236.1, JP237.7, U40.6, U40.16
GND40: C201.2, C202.2, C203.2, C204.2, C205.C, JP241.GND1, JP241.SHIELD1, JP241.SHIELD2, JP241.SHIELD3, JP242.1, JP243.7, U41.6, U41.16
GND41: C206.2, C207.2, C208.2, C209.2, C210.C, JP247.GND1, JP247.SHIELD1, JP247.SHIELD2, JP247.SHIELD3, JP248.1, JP249.7, U42.6, U42.16
GND42: C211.2, C212.2, C213.2, C214.2, C215.C, JP253.GND1, JP253.SHIELD1, JP253.SHIELD2, JP253.SHIELD3, JP254.1, JP255.7, U43.6, U43.16
GND43: C216.2, C217.2, C218.2, C219.2, C220.C, JP259.GND1, JP259.SHIELD1, JP259.SHIELD2, JP259.SHIELD3, JP260.1, JP261.7, U44.6, U44.16
GND44: C221.2, C222.2, C223.2, C224.2, C225.C, JP265.GND1, JP265.SHIELD1, JP265.SHIELD2, JP265.SHIELD3, JP266.1, JP267.7, U45.6, U45.16
GND45: C226.2, C227.2, C228.2, C229.2, C230.C, JP271.GND1, JP271.SHIELD1, JP271.SHIELD2, JP271.SHIELD3, JP272.1, JP273.7, U46.6, U46.16
GND46: C231.2, C232.2, C233.2, C234.2, C235.C, JP277.GND1, JP277.SHIELD1, JP277.SHIELD2, JP277.SHIELD3, JP278.1, JP279.7, U47.6, U47.16
GND47: C236.2, C237.2, C238.2, C239.2, C240.C, JP283.GND1, JP283.SHIELD1, JP283.SHIELD2, JP283.SHIELD3, JP284.1, JP285.7, U48.6, U48.16
GND48: C241.2, C242.2, C243.2, C244.2, C245.C, JP289.GND1, JP289.SHIELD1, JP289.SHIELD2, JP289.SHIELD3, JP290.1, JP291.7, U49.6, U49.16
GND49: C246.2, C247.2, C248.2, C249.2, C250.C, JP295.GND1, JP295.SHIELD1, JP295.SHIELD2, JP295.SHIELD3, JP296.1, JP297.7, U50.6, U50.16
GND50: C251.2, C252.2, C253.2, C254.2, C255.C, JP301.GND1, JP301.SHIELD1, JP301.SHIELD2, JP301.SHIELD3, JP302.1, JP303.7, U51.6, U51.16
GND51: C256.2, C257.2, C258.2, C259.2, C260.C, JP307.GND1, JP307.SHIELD1, JP307.SHIELD2, JP307.SHIELD3, JP308.1, JP309.7, U52.6, U52.16
GND52: C261.2, C262.2, C263.2, C264.2, C265.C, JP313.GND1, JP313.SHIELD1, JP313.SHIELD2, JP313.SHIELD3, JP314.1, JP315.7, U53.6, U53.16
GND53: C266.2, C267.2, C268.2, C269.2, C270.C, JP319.GND1, JP319.SHIELD1, JP319.SHIELD2, JP319.SHIELD3, JP320.1, JP321.7, U54.6, U54.16
GND54: C271.2, C272.2, C273.2, C274.2, C275.C, JP325.GND1, JP325.SHIELD1, JP325.SHIELD2, JP325.SHIELD3, JP326.1, JP327.7, U55.6, U55.16
GND55: C276.2, C277.2, C278.2, C279.2, C280.C, JP331.GND1, JP331.SHIELD1, JP331.SHIELD2, JP331.SHIELD3, JP332.1, JP333.7, U56.6, U56.16
unnamed: R1.2, U1.12
unnamed: R2.1, U1.11
unnamed: C3.1, JP1.D+1, R2.2
unnamed: C4.1, JP1.D-1, R1.1
unnamed: D2.C, R3.2
unnamed: D1.C, R4.2
unnamed: R3.1, SJ2.2
unnamed: R4.1, SJ3.2
unnamed: R7.2, U2.12
unnamed: R8.1, U2.11
unnamed: C7.1, JP7.D+1, R8.2
unnamed: C8.1, JP7.D-1, R7.1
unnamed: D4.C, R9.2
unnamed: D3.C, R10.2
unnamed: R9.1, SJ5.2
unnamed: R10.1, SJ6.2
unnamed: R13.2, U3.12
unnamed: R14.1, U3.11
unnamed: C12.1, JP13.D+1, R14.2
unnamed: C13.1, JP13.D-1, R13.1
unnamed: D6.C, R15.2
unnamed: D5.C, R16.2
unnamed: R15.1, SJ8.2
unnamed: R16.1, SJ9.2
unnamed: R19.2, U4.12
unnamed: R20.1, U4.11
unnamed: C17.1, JP19.D+1, R20.2
unnamed: C18.1, JP19.D-1, R19.1
unnamed: D8.C, R21.2
unnamed: D7.C, R22.2
unnamed: R21.1, SJ11.2
unnamed: R22.1, SJ12.2
unnamed: R25.2, U5.12
unnamed: R26.1, U5.11
unnamed: C22.1, JP25.D+1, R26.2
unnamed: C23.1, JP25.D-1, R25.1
unnamed: D10.C, R27.2
unnamed: D9.C, R28.2
unnamed: R27.1, SJ14.2
unnamed: R28.1, SJ15.2
unnamed: R31.2, U6.12
unnamed: R32.1, U6.11
unnamed: C27.1, JP31.D+1, R32.2
unnamed: C28.1, JP31.D-1, R31.1
unnamed: D12.C, R33.2
unnamed: D11.C, R34.2
unnamed: R33.1, SJ17.2
unnamed: R34.1, SJ18.2
unnamed: R37.2, U7.12
unnamed: R38.1, U7.11
unnamed: C32.1, JP37.D+1, R38.2
unnamed: C33.1, JP37.D-1, R37.1
unnamed: D14.C, R39.2
unnamed: D13.C, R40.2
unnamed: R39.1, SJ20.2
unnamed: R40.1, SJ21.2
unnamed: R43.2, U8.12
unnamed: R44.1, U8.11
unnamed: C37.1, JP43.D+1, R44.2
unnamed: C38.1, JP43.D-1, R43.1
unnamed: D16.C, R45.2
unnamed: D15.C, R46.2
unnamed: R45.1, SJ23.2
unnamed: R46.1, SJ24.2
unnamed: R49.2, U9.12
unnamed: R50.1, U9.11
unnamed: C42.1, JP49.D+1, R50.2
unnamed: C43.1, JP49.D-1, R49.1
unnamed: D18.C, R51.2
unnamed: D17.C, R52.2
unnamed: R51.1, SJ26.2
unnamed: R52.1, SJ27.2
unnamed: R55.2, U10.12
unnamed: R56.1, U10.11
unnamed: C47.1, JP55.D+1, R56.2
unnamed: C48.1, JP55.D-1, R55.1
unnamed: D20.C, R57.2
unnamed: D19.C, R58.2
unnamed: R57.1, SJ29.2
unnamed: R58.1, SJ30.2
unnamed: R61.2, U11.12
unnamed: R62.1, U11.11
unnamed: C52.1, JP61.D+1, R62.2
unnamed: C53.1, JP61.D-1, R61.1
unnamed: D22.C, R63.2
unnamed: D21.C, R64.2
unnamed: R63.1, SJ32.2
unnamed: R64.1, SJ33.2
unnamed: R67.2, U12.12
unnamed: R68.1, U12.11
unnamed: C57.1, JP67.D+1, R68.2
unnamed: C58.1, JP67.D-1, R67.1
unnamed: D24.C, R69.2
unnamed: D23.C, R70.2
unnamed: R69.1, SJ35.2
unnamed: R70.1, SJ36.2
unnamed: R73.2, U13.12
unnamed: R74.1, U13.11
unnamed: C62.1, JP73.D+1, R74.2
unnamed: C63.1, JP73.D-1, R73.1
unnamed: D26.C, R75.2
unnamed: D25.C, R76.2
unnamed: R75.1, SJ38.2
unnamed: R76.1, SJ39.2
unnamed: R79.2, U14.12
unnamed: R80.1, U14.11
unnamed: C67.1, JP79.D+1, R80.2
unnamed: C68.1, JP79.D-1, R79.1
unnamed: D28.C, R81.2
unnamed: D27.C, R82.2
unnamed: R81.1, SJ41.2
unnamed: R82.1, SJ42.2
unnamed: R85.2, U15.12
unnamed: R86.1, U15.11
unnamed: C72.1, JP85.D+1, R86.2
unnamed: C73.1, JP85.D-1, R85.1
unnamed: D30.C, R87.2
unnamed: D29.C, R88.2
unnamed: R87.1, SJ44.2
unnamed: R88.1, SJ45.2
unnamed: R91.2, U16.12
unnamed: R92.1, U16.11
unnamed: C77.1, JP91.D+1, R92.2
unnamed: C78.1, JP91.D-1, R91.1
unnamed: D32.C, R93.2
unnamed: D31.C, R94.2
unnamed: R93.1, SJ47.2
unnamed: R94.1, SJ48.2
unnamed: R97.2, U17.12
unnamed: R98.1, U17.11
unnamed: C82.1, JP97.D+1, R98.2
unnamed: C83.1, JP97.D-1, R97.1
unnamed: D34.C, R99.2
unnamed: D33.C, R100.2
unnamed: R99.1, SJ50.2
unnamed: R100.1, SJ51.2
unnamed: R103.2, U18.12
unnamed: R104.1, U18.11
unnamed: C87.1, JP103.D+1, R104.2
unnamed: C88.1, JP103.D-1, R103.1
unnamed: D36.C, R105.2
unnamed: D35.C, R106.2
unnamed: R105.1, SJ53.2
unnamed: R106.1, SJ54.2
unnamed: R109.2, U19.12
unnamed: R110.1, U19.11
unnamed: C92.1, JP109.D+1, R110.2
unnamed: C93.1, JP109.D-1, R109.1
unnamed: D38.C, R111.2
unnamed: D37.C, R112.2
unnamed: R111.1, SJ56.2
unnamed: R112.1, SJ57.2
unnamed: R115.2, U20.12
unnamed: R116.1, U20.11
unnamed: C97.1, JP115.D+1, R116.2
unnamed: C98.1, JP115.D-1, R115.1
unnamed: D40.C, R117.2
unnamed: D39.C, R118.2
unnamed: R117.1, SJ59.2
unnamed: R118.1, SJ60.2
unnamed: R121.2, U21.12
unnamed: R122.1, U21.11
unnamed: C102.1, JP121.D+1, R122.2
unnamed: C103.1, JP121.D-1, R121.1
unnamed: D42.C, R123.2
unnamed: D41.C, R124.2
unnamed: R123.1, SJ62.2
unnamed: R124.1, SJ63.2
unnamed: R127.2, U22.12
unnamed: R128.1, U22.11
unnamed: C107.1, JP127.D+1, R128.2
unnamed: C108.1, JP127.D-1, R127.1
unnamed: D44.C, R129.2
unnamed: D43.C, R130.2
unnamed: R129.1, SJ65.2
unnamed: R130.1, SJ66.2
unnamed: R133.2, U23.12
unnamed: R134.1, U23.11
unnamed: C112.1, JP133.D+1, R134.2
unnamed: C113.1, JP133.D-1, R133.1
unnamed: D46.C, R135.2
unnamed: D45.C, R136.2
unnamed: R135.1, SJ68.2
unnamed: R136.1, SJ69.2
unnamed: R139.2, U24.12
unnamed: R140.1, U24.11
unnamed: C117.1, JP139.D+1, R140.2
unnamed: C118.1, JP139.D-1, R139.1
unnamed: D48.C, R141.2
unnamed: D47.C, R142.2
unnamed: R141.1, SJ71.2
unnamed: R142.1, SJ72.2
unnamed: R145.2, U25.12
unnamed: R146.1, U25.11
unnamed: C122.1, JP145.D+1, R146.2
unnamed: C123.1, JP145.D-1, R145.1
unnamed: D50.C, R147.2
unnamed: D49.C, R148.2
unnamed: R147.1, SJ74.2
unnamed: R148.1, SJ75.2
unnamed: R151.2, U26.12
unnamed: R152.1, U26.11
unnamed: C127.1, JP151.D+1, R152.2
unnamed: C128.1, JP151.D-1, R151.1
unnamed: D52.C, R153.2
unnamed: D51.C, R154.2
unnamed: R153.1, SJ77.2
unnamed: R154.1, SJ78.2
unnamed: R157.2, U27.12
unnamed: R158.1, U27.11
unnamed: C132.1, JP157.D+1, R158.2
unnamed: C133.1, JP157.D-1, R157.1
unnamed: D54.C, R159.2
unnamed: D53.C, R160.2
unnamed: R159.1, SJ80.2
unnamed: R160.1, SJ81.2
unnamed: R163.2, U28.12
unnamed: R164.1, U28.11
unnamed: C137.1, JP163.D+1, R164.2
unnamed: C138.1, JP163.D-1, R163.1
unnamed: D56.C, R165.2
unnamed: D55.C, R166.2
unnamed: R165.1, SJ83.2
unnamed: R166.1, SJ84.2
unnamed: R169.2, U29.12
unnamed: R170.1, U29.11
unnamed: C142.1, JP169.D+1, R170.2
unnamed: C143.1, JP169.D-1, R169.1
unnamed: D58.C, R171.2
unnamed: D57.C, R172.2
unnamed: R171.1, SJ86.2
unnamed: R172.1, SJ87.2
unnamed: R175.2, U30.12
unnamed: R176.1, U30.11
unnamed: C147.1, JP175.D+1, R176.2
unnamed: C148.1, JP175.D-1, R175.1
unnamed: D60.C, R177.2
unnamed: D59.C, R178.2
unnamed: R177.1, SJ89.2
unnamed: R178.1, SJ90.2
unnamed: R181.2, U31.12
unnamed: R182.1, U31.11
unnamed: C152.1, JP181.D+1, R182.2
unnamed: C153.1, JP181.D-1, R181.1
unnamed: D62.C, R183.2
unnamed: D61.C, R184.2
unnamed: R183.1, SJ92.2
unnamed: R184.1, SJ93.2
unnamed: R187.2, U32.12
unnamed: R188.1, U32.11
unnamed: C157.1, JP187.D+1, R188.2
unnamed: C158.1, JP187.D-1, R187.1
unnamed: D64.C, R189.2
unnamed: D63.C, R190.2
unnamed: R189.1, SJ95.2
unnamed: R190.1, SJ96.2
unnamed: R193.2, U33.12
unnamed: R194.1, U33.11
unnamed: C162.1, JP193.D+1, R194.2
unnamed: C163.1, JP193.D-1, R193.1
unnamed: D66.C, R195.2
unnamed: D65.C, R196.2
unnamed: R195.1, SJ98.2
unnamed: R196.1, SJ99.2
unnamed: R199.2, U34.12
unnamed: R200.1, U34.11
unnamed: C167.1, JP199.D+1, R200.2
unnamed: C168.1, JP199.D-1, R199.1
unnamed: D68.C, R201.2
unnamed: D67.C, R202.2
unnamed: R201.1, SJ101.2
unnamed: R202.1, SJ102.2
unnamed: R205.2, U35.12
unnamed: R206.1, U35.11
unnamed: C172.1, JP205.D+1, R206.2
unnamed: C173.1, JP205.D-1, R205.1
unnamed: D70.C, R207.2
unnamed: D69.C, R208.2
unnamed: R207.1, SJ104.2
unnamed: R208.1, SJ105.2
unnamed: R211.2, U36.12
unnamed: R212.1, U36.11
unnamed: C177.1, JP211.D+1, R212.2
unnamed: C178.1, JP211.D-1, R211.1
unnamed: D72.C, R213.2
unnamed: D71.C, R214.2
unnamed: R213.1, SJ107.2
unnamed: R214.1, SJ108.2
unnamed: R217.2, U37.12
unnamed: R218.1, U37.11
unnamed: C182.1, JP217.D+1, R218.2
unnamed: C183.1, JP217.D-1, R217.1
unnamed: D74.C, R219.2
unnamed: D73.C, R220.2
unnamed: R219.1, SJ110.2
unnamed: R220.1, SJ111.2
unnamed: R223.2, U38.12
unnamed: R224.1, U38.11
unnamed: C187.1, JP223.D+1, R224.2
unnamed: C188.1, JP223.D-1, R223.1
unnamed: D76.C, R225.2
unnamed: D75.C, R226.2
unnamed: R225.1, SJ113.2
unnamed: R226.1, SJ114.2
unnamed: R229.2, U39.12
unnamed: R230.1, U39.11
unnamed: C192.1, JP229.D+1, R230.2
unnamed: C193.1, JP229.D-1, R229.1
unnamed: D78.C, R231.2
unnamed: D77.C, R232.2
unnamed: R231.1, SJ116.2
unnamed: R232.1, SJ117.2
unnamed: R235.2, U40.12
unnamed: R236.1, U40.11
unnamed: C197.1, JP235.D+1, R236.2
unnamed: C198.1, JP235.D-1, R235.1
unnamed: D80.C, R237.2
unnamed: D79.C, R238.2
unnamed: R237.1, SJ119.2
unnamed: R238.1, SJ120.2
unnamed: R241.2, U41.12
unnamed: R242.1, U41.11
unnamed: C202.1, JP241.D+1, R242.2
unnamed: C203.1, JP241.D-1, R241.1
unnamed: D82.C, R243.2
unnamed: D81.C, R244.2
unnamed: R243.1, SJ122.2
unnamed: R244.1, SJ123.2
unnamed: R247.2, U42.12
unnamed: R248.1, U42.11
unnamed: C207.1, JP247.D+1, R248.2
unnamed: C208.1, JP247.D-1, R247.1
unnamed: D84.C, R249.2
unnamed: D83.C, R250.2
unnamed: R249.1, SJ125.2
unnamed: R250.1, SJ126.2
unnamed: R253.2, U43.12
unnamed: R254.1, U43.11
unnamed: C212.1, JP253.D+1, R254.2
unnamed: C213.1, JP253.D-1, R253.1
unnamed: D86.C, R255.2
unnamed: D85.C, R256.2
unnamed: R255.1, SJ128.2
unnamed: R256.1, SJ129.2
unnamed: R259.2, U44.12
unnamed: R260.1, U44.11
unnamed: C217.1, JP259.D+1, R260.2
unnamed: C218.1, JP259.D-1, R259.1
unnamed: D88.C, R261.2
unnamed: D87.C, R262.2
unnamed: R261.1, SJ131.2
unnamed: R262.1, SJ132.2
unnamed: R265.2, U45.12
unnamed: R266.1, U45.11
unnamed: C222.1, JP265.D+1, R266.2
unnamed: C223.1, JP265.D-1, R265.1
unnamed: D90.C, R267.2
unnamed: D89.C, R268.2
unnamed: R267.1, SJ134.2
unnamed: R268.1, SJ135.2
unnamed: R271.2, U46.12
unnamed: R272.1, U46.11
unnamed: C227.1, JP271.D+1, R272.2
unnamed: C228.1, JP271.D-1, R271.1
unnamed: D92.C, R273.2
unnamed: D91.C, R274.2
unnamed: R273.1, SJ137.2
unnamed: R274.1, SJ138.2
unnamed: R277.2, U47.12
unnamed: R278.1, U47.11
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
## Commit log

2013-02-15 Initial hardware commit (v01)
2013-02-18 Updated micro USB connector
    This is Pete's micro-USB package, which has two more pads under the
    connector to solidify the physical connection.
2013-02-18 Removing BOM
2013-03-15 Silkscreen fixes: no-silk headers, moved labels
2013-03-18 Added fiducials, minor silkscreen changes.
2013-03-19 Production readiness
    Created panel of boards. Adjusted fiducial position.
2013-05-10 Update README.md
    Updating readme to include product links, info, and pictures.
2013-05-10 Update README.md
    Adding bit about production files directory.
2014-10-29 Updated footprints, sch, microb
    Updated to 0603 components
    Updated to bossed microb
    Trace reroutes
2014-10-30 Fixed y junction
2014-11-18 Updated USB with Staking vias
2014-12-19 Initial QC CL, Updated Parts, Fixed SCH.
2015-04-15 Files re up
2015-05-01 Silk Change
2015-07-28 Adding sch notes, small silk edits, small trace fix
    Adding notes for VIN and jumper usage. Also made some small silk edits
    to avoid silk getting cut off by vias. Had to make one small trace
    change on 3.3V net to avoid natural bridge between pads 13 and 14.
2015-07-28 Via drills change, moved R6 and library package update
    Dropped all vias excepting the 3 usb connector staking vias to 15 mil to
    jive better with silk. Moved R6 further in from edge of board to avoid
    DPN damage/danger. Ran library update to include polarity mark silk
    edits to SSOP20 package. Bumped micro-fiducials up to full fiducial
    size.
2015-08-14 Fixing issues from design checklist
    See issue #4 in repo for full rundown.
2015-08-14 Fixed bstop issue
    removed weird bstop lines near jumpers.
2015-10-21 Changed PCB dimension
    Increased PCB dimension to better support USB connector. Also slightly
    adjusted the connector location itself to sit correctly on the PCB edge.
2015-10-22 Moved design to 0,0 on grid and v number
    Per QC review: moved design to 0 of XY grid in brd file and moved
    version number to edge of board.
2015-12-29 Updating DRC to new "TIGHT" dru
    Migrating over to the newest set of drus. Using TIGHT dru for this
    product.
2016-01-04 Fixes to PROD_IDs on JP1, R3 and R4
    Now they all have the correct PROD_ID for the part.
2016-01-07 created panel v11
2025-06-27 Update README.md
    Updating link
